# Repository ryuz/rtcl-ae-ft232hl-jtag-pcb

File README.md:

# FT232HLを JTAG 用に変換する基板

[English](README_en.md)

秋月電子さんの[FT232HL ハイスピードUSBシリアル変換モジュール](https://akizukidenshi.com/catalog/g/g106503/) を、JTAG 用に変換する基板を作りました。

主に拙作の [Tang Primer25K用USB3.0基板](https://github.com/ryuz/rtcl-tp25k-usb3-pcb) で利用することを想定しています。

一本づつ繋がなくて良くなるので、抜き差しがとても楽になります。

## 使い方

使用時の利便性を加味して、半田面にもシルク印刷していますので、コネクタを半田付けするときは表裏を間違えないように注意してください。

J1/J2/J3 などのリファレンスが印字されている側が部品面です。

FT232HL ハイスピードUSBシリアル変換モジュールは側は JP3 のみショートさせ、 **JP4は必ずオープンにしてください**。

JP4は I/O 電圧を供給するものですが、今回は接続先のボードから電圧を取るように設計しており、もし JP4 を繋ぐと FT232HL 側からも 3.3V電圧が供給されてしまい電源電圧の衝突で **ボードが壊れる可能性** があります。

## 免責事項

本設計データは、研究開発用の試作実験に用するものであり、利用に際して発生した如何なる損害も作者は補償いたしませんので予めご了承ください。

## ライセンス(License)

本設計データは、[クリエイティブ・コモンズ 表示-非営利 4.0 国際 ライセンス](https://creativecommons.org/licenses/by-nc/4.0/deed.ja)の下で提供されています。

製造した本基板の無断での販売や配布を行わない限りは、趣味や研究開発用途でご自由にお使いいただく事が出来ます。

また、商用に製造販売を希望される場合は、別途ライセンス契約を作者までご相談ください。[お問い合わせフォーム](https://rtc-lab.com/contact/)などからお問い合わせ頂けます。

## 作者情報

渕上 竜司(Ryuji Fuchikami)
[リアルタイムコンピューティング研究所](https://rtc-lab.com/)

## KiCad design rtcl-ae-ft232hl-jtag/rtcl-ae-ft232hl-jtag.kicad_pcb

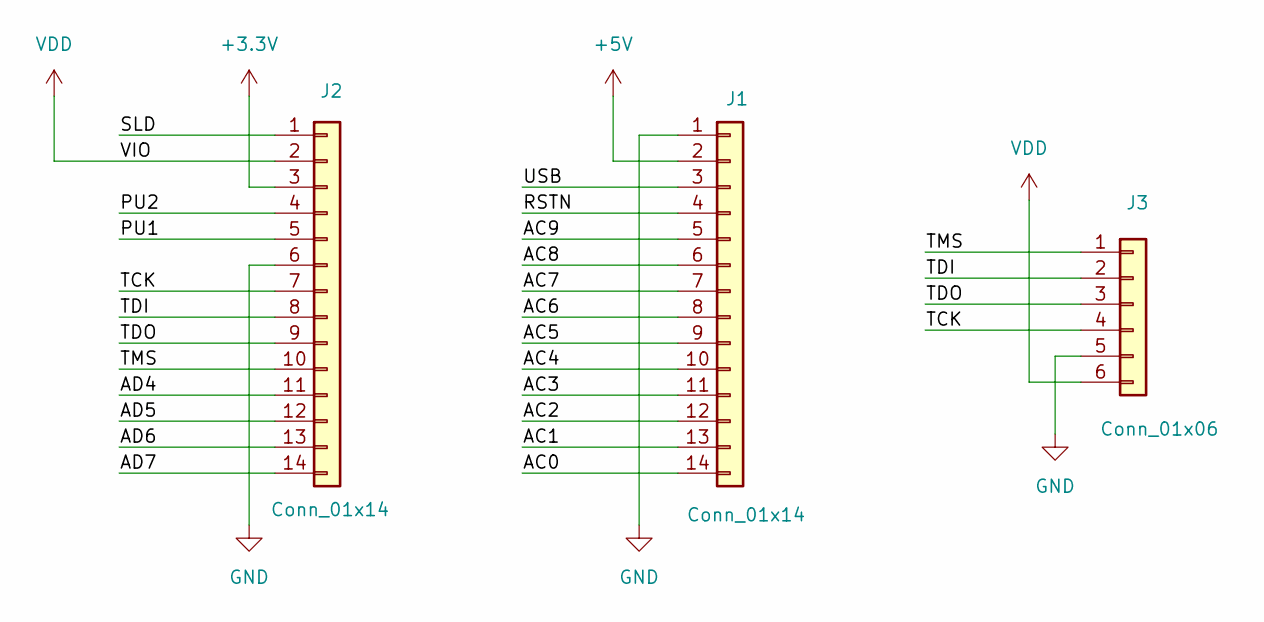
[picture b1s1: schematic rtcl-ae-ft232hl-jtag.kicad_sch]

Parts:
J1, J2: Conn_01x14; PinSocket_1x14_P2.54mm_Vertical
J3: Conn_01x06; PinSocket_1x06_P2.54mm_Horizontal

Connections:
+3.3V: J2.3
+5V: J1.2
/AC0: J1.14
/AC1: J1.13
/AC2: J1.12
/AC3: J1.11
/AC4: J1.10
/AC5: J1.9
/AC6: J1.8
/AC7: J1.7
/AC8: J1.6
/AC9: J1.5
/AD4: J2.11
/AD5: J2.12
/AD6: J2.13
/AD7: J2.14
/PU1: J2.5
/PU2: J2.4
/RSTN: J1.4
/SLD: J2.1
/TCK: J2.7, J3.4
/TDI: J2.8, J3.2
/TDO: J2.9, J3.3
/TMS: J2.10, J3.1
/USB: J1.3
GND: J1.1, J2.6, J3.5
VDD: J2.2, J3.6

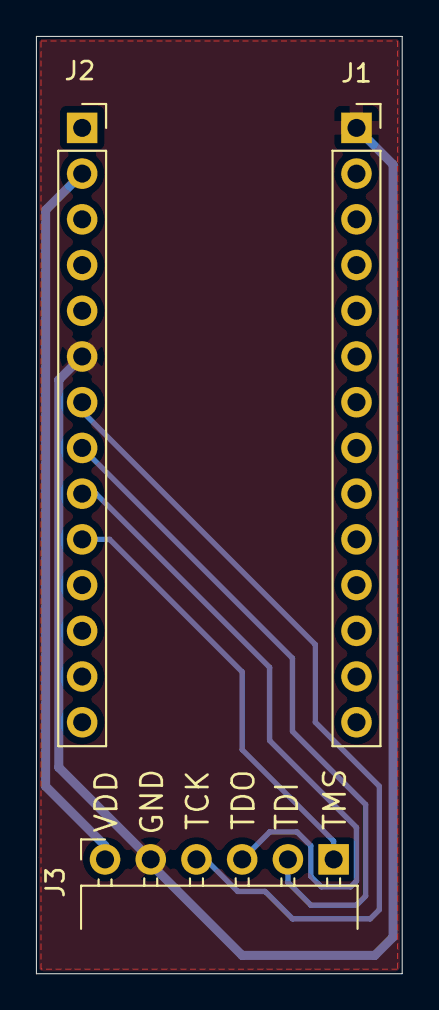
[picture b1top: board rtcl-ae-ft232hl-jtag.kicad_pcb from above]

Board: 2 copper layers, 20.3 x 52.1 mm, 3 parts (0 on the bottom side), 6 nets.

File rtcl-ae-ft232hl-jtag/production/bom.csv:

Designator,Footprint,Quantity,Value,LCSC Part #
"J1, J2",PinSocket_1x14_P2.54mm_Vertical,2,Conn_01x14,
J3,PinSocket_1x06_P2.54mm_Horizontal,1,Conn_01x06,

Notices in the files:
rtcl-ae-ft232hl-jtag/rtcl-ae-ft232hl-jtag.kicad_pcb:
© RTC-Lab
